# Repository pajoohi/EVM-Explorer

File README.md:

# TI EVM Explorer

A highly modular, premium-designed web application for browsing and inspecting Texas Instruments Hardware Development Kits (EVMs). 

## Features
- **Filterable/Searchable Directory**: Quickly locate evaluation modules by Processor or Board Family.
- **Detailed EVM Pages**: Dynamic specs, integrated interactive BOMs, OS downloads, and rich 3D STL visualizations.
- **Responsive & Accessible**: Native Light/Dark modes, mobile-friendly navigation, and CSS-driven component animations.

## Local Development
1. Install dependencies: `npm install`
2. Start the development server: `npm run dev`

## Deployment (GitHub Pages)
This project is configured for seamless deployment to GitHub pages using Vite and `gh-pages`.

1. Ensure the `base` property in `vite.config.js` matches your repository name (e.g., `'/EVM-Explorer/'`).
2. Run the deployment script: `npm run deploy`
   - This automatically builds the production output to the `dist/` folder and pushes it to the `gh-pages` branch.

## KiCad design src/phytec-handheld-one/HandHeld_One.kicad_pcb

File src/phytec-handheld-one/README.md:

# PHYTEC Handheld One

The **PHYTEC Handheld One** is a functional handheld gaming device developed in under six weeks as a proof-of-concept for PHYTEC's System-on-Module (SoM) design approach, and showcased at **Embedded World**. It demonstrates how pre-engineered hardware can accelerate the journey from a breadboard prototype to a custom, bootable system.

## Overview

This repository contains the design files and documentation used to build the Handheld One. The project highlights the advantages of using a SOM over a discrete chip-down design, allowing for rapid iteration and scalability.

## Key Features

* **Rapid prototyping:** Concept to custom carrier board in under six weeks.
* **Gaming-ready Linux stack:** RetroArch (GLES3) with libretro cores, Freedoom, Chocolate Doom, SuperTuxKart, and Neverball, all launched from a custom touchscreen UI.
* **Integrated peripherals:** Touchscreen, gamepad inputs (D-pad / face buttons) via the MSPM0 companion MCU.

## Hardware Architecture

The Handheld One is built around the PHYTEC SOM ecosystem. By utilizing a standardized footprint, the carrier board can accommodate different performance tiers without requiring a complete redesign.

Designed in **KiCad 9.0**, the Schematics (`.kicad_sch`) and PCB layout (`.kicad_pcb`) live in the hardware repo below.

## Software

The Handheld One runs a **Yocto** based Linux distribution (scarthgap). The `meta-handheld-one` layer pulls in the launcher, retro gaming stack, Wayland/Weston graphics, and the AM62Px 3D demo.

## Repositories

- **[`phytec-handheld-one`](https://github.com/phytec-labs/phytec-handheld-one)** — Hardware design (KiCad schematics and PCB layout)
- **[`meta-handheld-one`](https://github.com/phytec-labs/meta-handheld-one/tree/scarthgap)** — Yocto meta-layer that builds the full image (use the `manifests` branch for repo-based checkout)
- **[`phytec-handheld-launcher`](https://github.com/phytec-labs/phytec-handheld-launcher/tree/scarthgap)** — Touchscreen launcher that runs at boot and starts the gaming stack
- **[`phytec-handheld-mspm0-driver`](https://github.com/phytec-labs/phytec-handheld-mspm0-driver)** — Firmware/drivers for the MSPM0 companion MCU (flashed manually, outside Yocto)

## Getting Started

Clone whichever piece you need:

```bash
# Hardware (KiCad 9.0+)
git clone https://github.com/phytec-labs/phytec-handheld-one.git

# Yocto BSP layer (scarthgap)
git clone -b scarthgap https://github.com/phytec-labs/meta-handheld-one.git

# Launcher
git clone -b scarthgap https://github.com/phytec-labs/phytec-handheld-launcher.git

# MSPM0 firmware
git clone https://github.com/phytec-labs/phytec-handheld-mspm0-driver.git
```

For a full Yocto build, use the `manifests` branch of `meta-handheld-one` to fetch all required layers via `phyLinux init -x`.

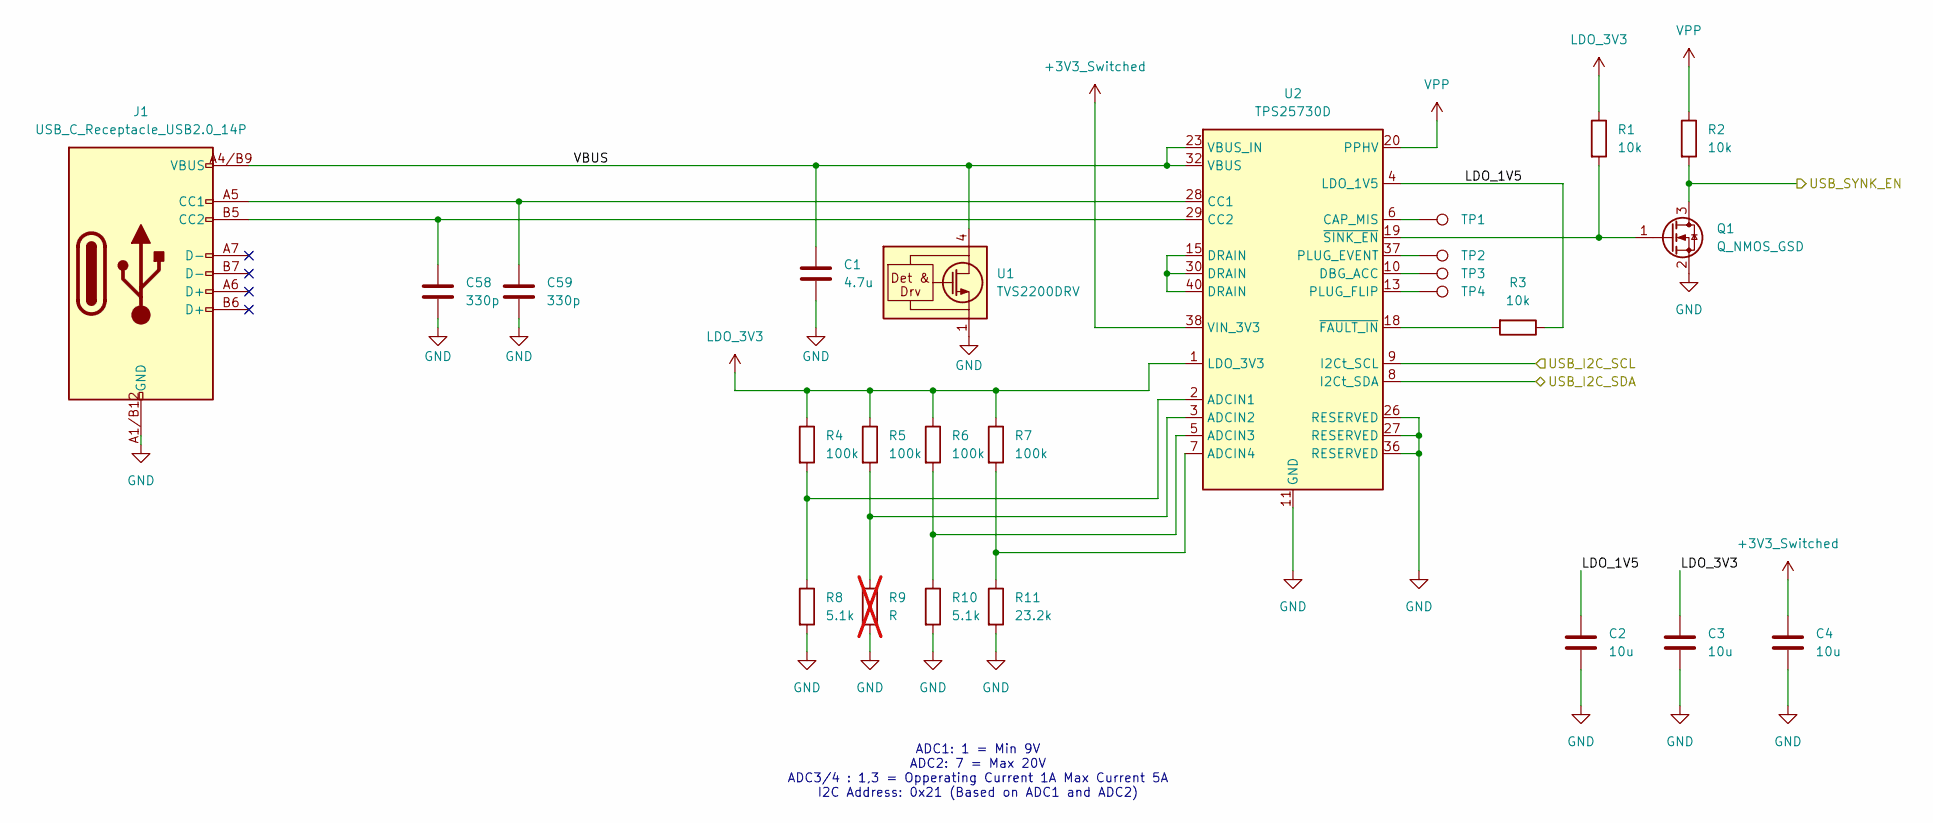
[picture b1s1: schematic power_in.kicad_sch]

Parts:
C1: 4.7u; C_0402_1005Metric_Pad0.74x0.62mm_HandSolder
C2, C3, C4: 10u; C_0402_1005Metric_Pad0.74x0.62mm_HandSolder
C58, C59: 330p; C_0402_1005Metric_Pad0.74x0.62mm_HandSolder
J1: USB_C_Receptacle_USB2.0_14P; CONN_8p94X6p5X3p16_12L_GCC
Q1: Q_NMOS_GSD; SC-59_Handsoldering
R1, R2, R3: 10k; R_0402_1005Metric_Pad0.72x0.64mm_HandSolder
R4, R5, R6, R7: 100k; R_0402_1005Metric_Pad0.72x0.64mm_HandSolder
R8, R10: 5.1k; R_0402_1005Metric_Pad0.72x0.64mm_HandSolder
R9: R; R_0402_1005Metric_Pad0.72x0.64mm_HandSolder; not fitted
R11: 23.2k; R_0402_1005Metric_Pad0.72x0.64mm_HandSolder
TP1, TP2, TP3, TP4: TestPoint; TestPoint_Pad_D1.0mm
U1: TVS2200DRV; WSON-6-1EP_2x2mm_P0.65mm_EP1x1.6mm
U2: TPS25730D; Texas_REF0038A_WQFN-38-2EP_6x4mm_P0.4

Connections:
+3V3_Switched: C4.1, U2.38 (VIN_3V3); also elsewhere on the board
/Audio/Audio_I2C_SCL: U2.9 (I2Ct_SCL); also elsewhere on the board
/Audio/Audio_I2C_SDA: U2.8 (I2Ct_SDA); also elsewhere on the board
/Power In/LDO_1V5: C2.1, R3.1, U2.4 (LDO_1V5)
/Power In/USB_SYNK_EN: Q1.3 (D), R2.2; also elsewhere on the board
/Power In/VBUS: C1.1, J1.A4/B9 (VBUS), J1.B4/A9 (VBUS), U1.4 (IN), U1.5 (IN), U1.6 (IN), U2.23 (VBUS_IN), U2.32 (VBUS)
GND: C1.2, C2.2, C3.2, C4.2, C58.2, C59.2, J1.A1/B12 (GND), J1.B1/A12 (GND), Q1.2 (S), R8.2, R9.2, R10.2, R11.2, U1.1 (GND), U1.2 (GND), U1.3 (GND), U1.7 (GND), U2.11 (GND), U2.12 (GND), U2.14 (GND), U2.16 (GND), U2.17 (GND), U2.26 (RESERVED), U2.27 (RESERVED), U2.31 (GND), U2.34 (GND), U2.36 (RESERVED), U2.39 (GND); also elsewhere on the board
LDO_3V3: C3.1, R1.1, R4.1, R5.1, R6.1, R7.1, U2.1 (LDO_3V3)
unnamed: C59.1, J1.A5 (CC1), U2.28 (CC1)
unnamed: C58.1, J1.B5 (CC2), U2.29 (CC2)
unnamed: Q1.1 (G), R1.2, U2.19 (~SINK_EN)
unnamed: R4.2, R8.1, U2.2 (ADCIN1)
unnamed: R5.2, R9.1, U2.3 (ADCIN2)
unnamed: R6.2, R10.1, U2.5 (ADCIN3)
unnamed: R7.2, R11.1, U2.7 (ADCIN4)
unnamed: TP1.1, U2.6 (CAP_MIS)
unnamed: TP3.1, U2.10 (DBG_ACC)
unnamed: U2.15 (DRAIN), U2.30 (DRAIN), U2.40 (DRAIN)
unnamed: TP2.1, U2.37 (PLUG_EVENT)
unnamed: TP4.1, U2.13 (PLUG_FLIP)
unnamed: R3.2, U2.18 (~FAULT_IN)
VPP: R2.1, U2.20 (PPHV); also elsewhere on the board

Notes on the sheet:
ADC1: 1 = Min 9V ADC2: 7 = Max 20V ADC3/4 : 1,3 = Opperating Current 1A Max Current 5A I2C Address: 0x21 (Based on ADC1 and ADC2)

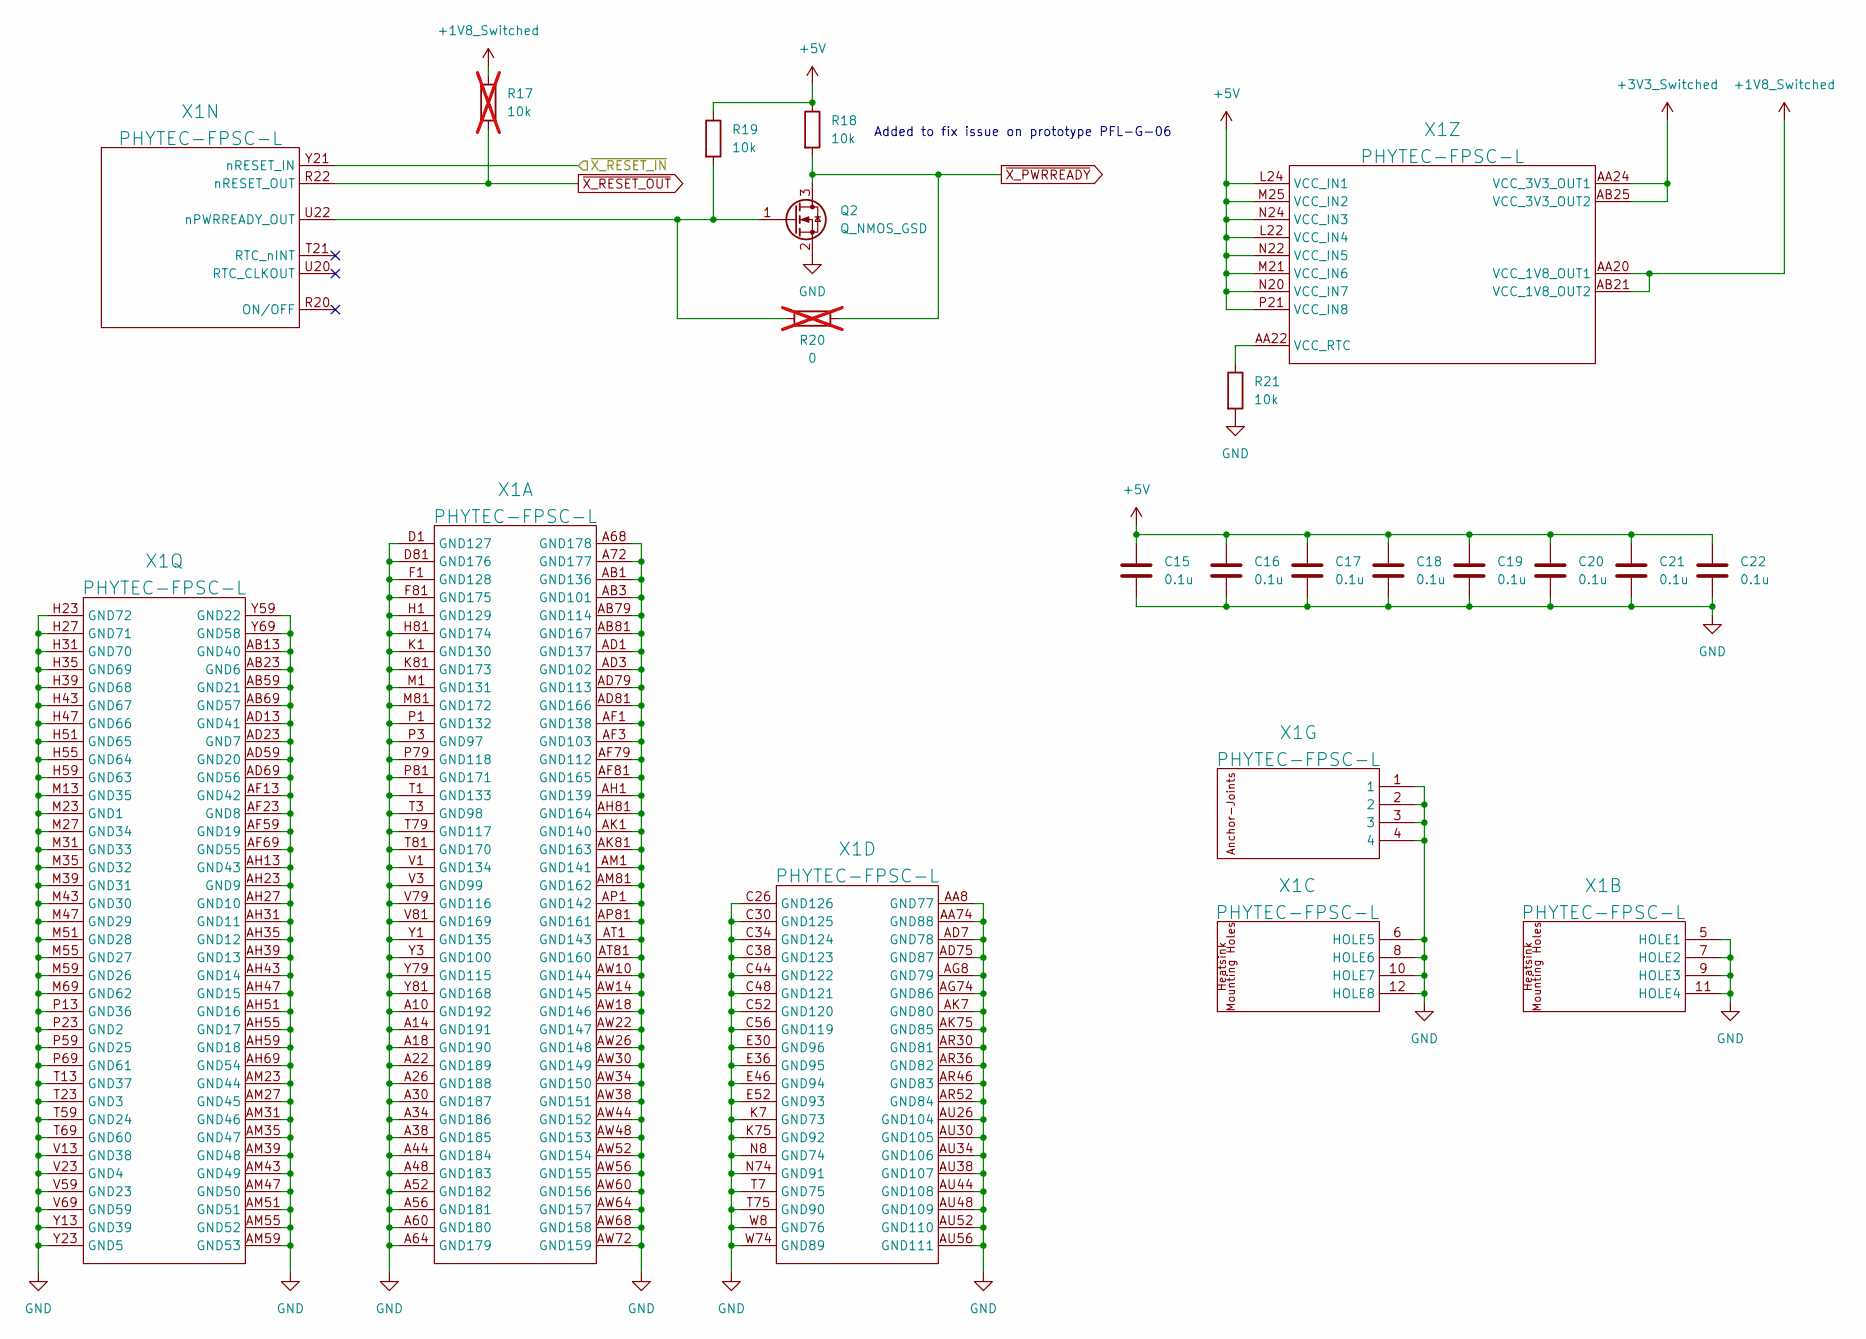
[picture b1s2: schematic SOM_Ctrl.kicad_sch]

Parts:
C15, C16, C17, C18, C19, C20, C21, C22: 0.1u; C_0402_1005Metric_Pad0.74x0.62mm_HandSolder
Q2: Q_NMOS_GSD; SC-59_Handsoldering
R17: 10k; R_0402_1005Metric_Pad0.72x0.64mm_HandSolder; not fitted
R18, R19, R21: 10k; R_0402_1005Metric_Pad0.72x0.64mm_HandSolder
R20: 0; R_0402_1005Metric_Pad0.72x0.64mm_HandSolder; not fitted
X1: PHYTEC-FPSC-L; PHYTEC-FPSC-BASIS-L-Socket

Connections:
+1V8_Switched: R17.1, X1.AA20 (VCC_1V8_OUT1), X1.AB21 (VCC_1V8_OUT2); also elsewhere on the board
+3V3_Switched: X1.AA24 (VCC_3V3_OUT1), X1.AB25 (VCC_3V3_OUT2); also elsewhere on the board
+5V: C15.1, C16.1, C17.1, C18.1, C19.1, C20.1, C21.1, C22.1, R18.1, R19.1, X1.L22 (VCC_IN4), X1.L24 (VCC_IN1), X1.M21 (VCC_IN6), X1.M25 (VCC_IN2), X1.N20 (VCC_IN7), X1.N22 (VCC_IN5), X1.N24 (VCC_IN3), X1.P21 (VCC_IN8); also elsewhere on the board
/Powre Reg/PGOOD: X1.Y21 (nRESET_IN); also elsewhere on the board
GND: C15.2, C16.2, C17.2, C18.2, C19.2, C20.2, C21.2, C22.2, Q2.2 (S), R21.2, X1.1, X1.2, X1.3, X1.4, X1.5 (HOLE1), X1.6 (HOLE5), X1.7 (HOLE2), X1.8 (HOLE6), X1.9 (HOLE3), X1.10 (HOLE7), X1.11 (HOLE4), X1.12 (HOLE8), X1.A10 (GND192), X1.A14 (GND191), X1.A18 (GND190), X1.A22 (GND189), X1.A26 (GND188), X1.A30 (GND187), X1.A34 (GND186), X1.A38 (GND185), X1.A44 (GND184), X1.A48 (GND183), X1.A52 (GND182), X1.A56 (GND181), X1.A60 (GND180), X1.A64 (GND179), X1.A68 (GND178), X1.A72 (GND177), X1.AA8 (GND77), X1.AA74 (GND88), X1.AB1 (GND136), X1.AB3 (GND101), X1.AB13 (GND40), X1.AB23 (GND6), X1.AB59 (GND21), X1.AB69 (GND57), X1.AB79 (GND114), X1.AB81 (GND167), X1.AD1 (GND137), X1.AD3 (GND102), X1.AD7 (GND78), X1.AD13 (GND41), X1.AD23 (GND7), X1.AD59 (GND20), X1.AD69 (GND56), X1.AD75 (GND87), X1.AD79 (GND113), X1.AD81 (GND166), X1.AF1 (GND138), X1.AF3 (GND103), X1.AF13 (GND42), X1.AF23 (GND8), X1.AF59 (GND19), X1.AF69 (GND55), X1.AF79 (GND112), X1.AF81 (GND165), X1.AG8 (GND79), X1.AG74 (GND86), X1.AH1 (GND139), X1.AH13 (GND43), X1.AH23 (GND9), X1.AH27 (GND10), X1.AH31 (GND11), X1.AH35 (GND12), X1.AH39 (GND13), X1.AH43 (GND14), X1.AH47 (GND15), X1.AH51 (GND16), X1.AH55 (GND17), X1.AH59 (GND18), X1.AH69 (GND54), X1.AH81 (GND164), X1.AK1 (GND140), X1.AK7 (GND80), X1.AK75 (GND85), X1.AK81 (GND163), X1.AM1 (GND141), X1.AM23 (GND44), X1.AM27 (GND45), X1.AM31 (GND46), X1.AM35 (GND47), X1.AM39 (GND48), X1.AM43 (GND49), X1.AM47 (GND50), X1.AM51 (GND51), X1.AM55 (GND52), X1.AM59 (GND53), X1.AM81 (GND162), X1.AP1 (GND142), X1.AP81 (GND161), X1.AR30 (GND81), X1.AR36 (GND82), X1.AR46 (GND83), X1.AR52 (GND84), X1.AT1 (GND143), X1.AT81 (GND160), X1.AU26 (GND104), X1.AU30 (GND105), X1.AU34 (GND106), X1.AU38 (GND107), X1.AU44 (GND108), X1.AU48 (GND109), X1.AU52 (GND110), X1.AU56 (GND111), X1.AW10 (GND144), X1.AW14 (GND145), X1.AW18 (GND146), X1.AW22 (GND147), X1.AW26 (GND148), X1.AW30 (GND149), X1.AW34 (GND150), X1.AW38 (GND151), X1.AW44 (GND152), X1.AW48 (GND153), X1.AW52 (GND154), X1.AW56 (GND155), X1.AW60 (GND156), X1.AW64 (GND157), X1.AW68 (GND158), X1.AW72 (GND159), X1.C26 (GND126), X1.C30 (GND125), X1.C34 (GND124), X1.C38 (GND123), X1.C44 (GND122), X1.C48 (GND121), X1.C52 (GND120), X1.C56 (GND119), X1.D1 (GND127), X1.D81 (GND176), X1.E30 (GND96), X1.E36 (GND95), X1.E46 (GND94), X1.E52 (GND93), X1.F1 (GND128), X1.F81 (GND175), X1.H1 (GND129), X1.H23 (GND72), X1.H27 (GND71), X1.H31 (GND70), X1.H35 (GND69), X1.H39 (GND68), X1.H43 (GND67), X1.H47 (GND66), X1.H51 (GND65), X1.H55 (GND64), X1.H59 (GND63), X1.H81 (GND174), X1.K1 (GND130), X1.K7 (GND73), X1.K75 (GND92), X1.K81 (GND173), X1.M1 (GND131), X1.M13 (GND35), X1.M23 (GND1), X1.M27 (GND34), X1.M31 (GND33), X1.M35 (GND32), X1.M39 (GND31), X1.M43 (GND30), X1.M47 (GND29), X1.M51 (GND28), X1.M55 (GND27), X1.M59 (GND26), X1.M69 (GND62), X1.M81 (GND172), X1.N8 (GND74), X1.N74 (GND91), X1.P1 (GND132), X1.P3 (GND97), X1.P13 (GND36), X1.P23 (GND2), X1.P59 (GND25), X1.P69 (GND61), X1.P79 (GND118), X1.P81 (GND171), X1.T1 (GND133), X1.T3 (GND98), X1.T7 (GND75), X1.T13 (GND37), X1.T23 (GND3), X1.T59 (GND24), X1.T69 (GND60), X1.T75 (GND90), X1.T79 (GND117), X1.T81 (GND170), X1.V1 (GND134), X1.V3 (GND99), X1.V13 (GND38), X1.V23 (GND4), X1.V59 (GND23), X1.V69 (GND59), X1.V79 (GND116), X1.V81 (GND169), X1.W8 (GND76), X1.W74 (GND89), X1.Y1 (GND135), X1.Y3 (GND100), X1.Y13 (GND39), X1.Y23 (GND5), X1.Y59 (GND22), X1.Y69 (GND58), X1.Y79 (GND115), X1.Y81 (GND168); also elsewhere on the board
unnamed: Q2.1 (G), R19.2, R20.1, X1.U22 (nPWRREADY_OUT)
unnamed: R21.1, X1.AA22 (VCC_RTC)
~X_PWRREADY: Q2.3 (D), R18.2, R20.2; also elsewhere on the board
~X_RESET_OUT: R17.2, X1.R22 (nRESET_OUT); also elsewhere on the board

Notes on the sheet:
Added to fix issue on prototype PFL-G-06

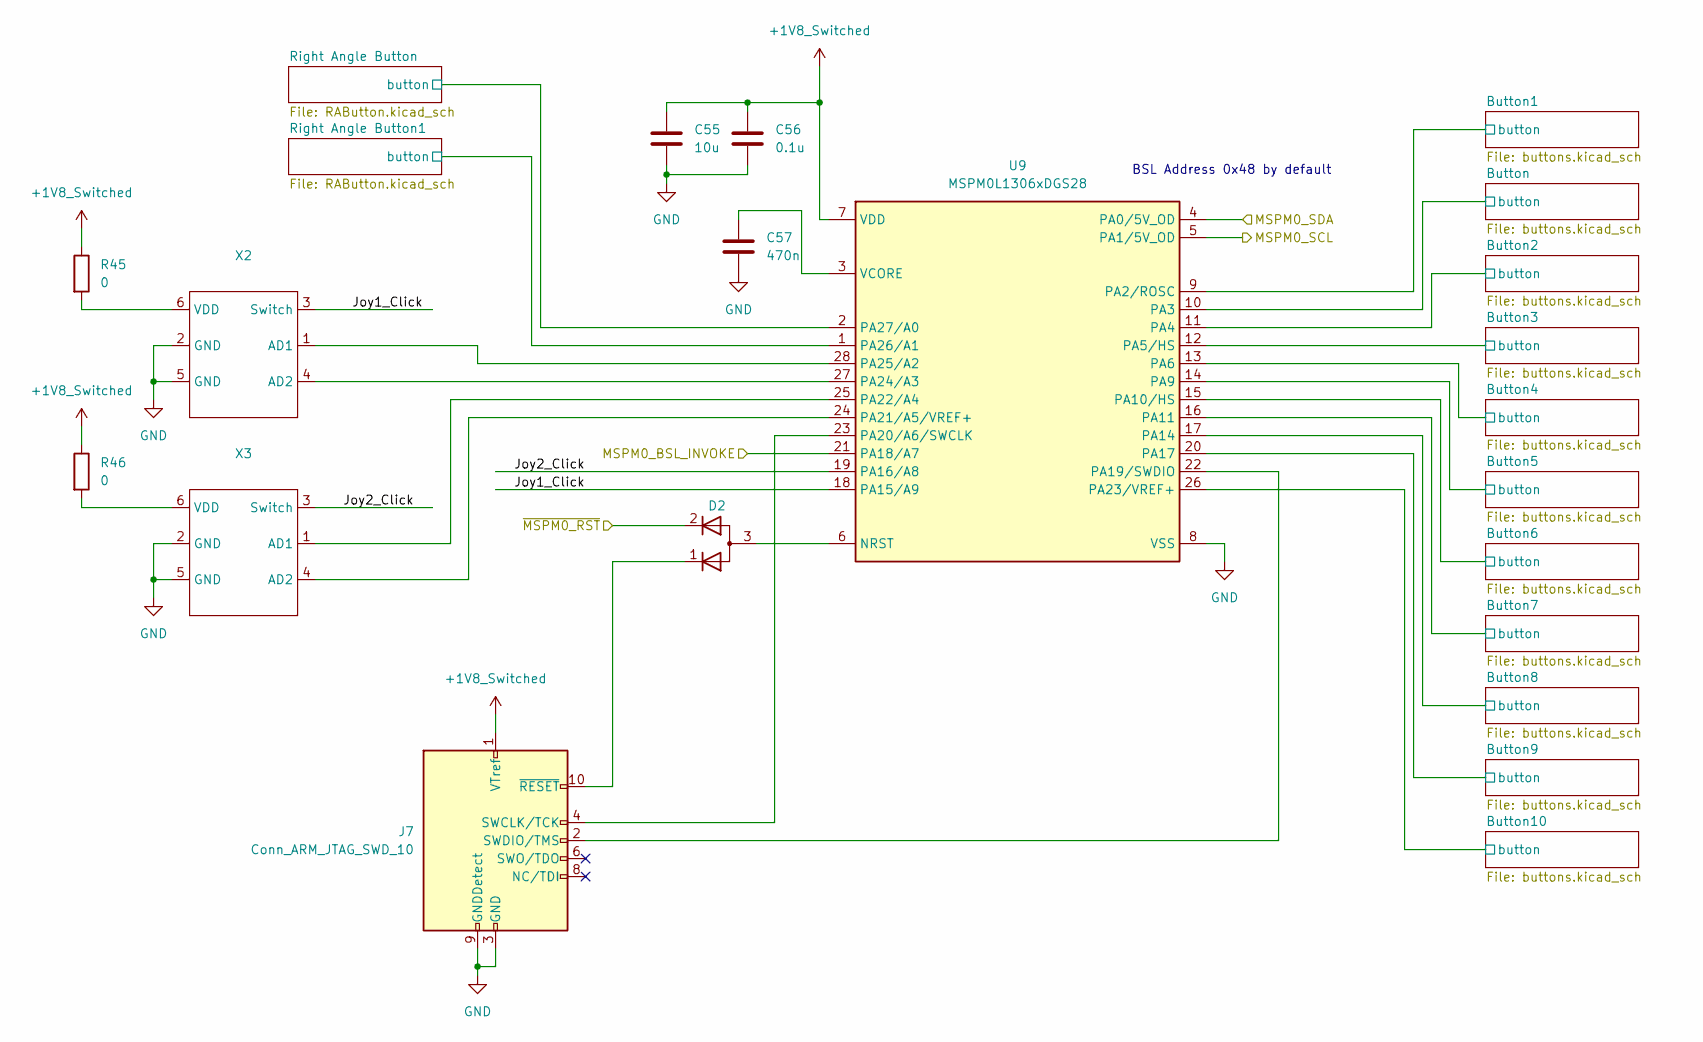
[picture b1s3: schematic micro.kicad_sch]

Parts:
C55: 10u; C_0402_1005Metric_Pad0.74x0.62mm_HandSolder
C56: 0.1u; C_0402_1005Metric_Pad0.74x0.62mm_HandSolder
C57: 470n; C_0402_1005Metric_Pad0.74x0.62mm_HandSolder
D2: D_Dual_CommonAnode_KKA_Parallel; SC-59_Handsoldering
J7: Conn_ARM_JTAG_SWD_10; PinHeader_2x05_P1.27mm_Vertical_SMD
R45, R46: 0; R_0402_1005Metric_Pad0.72x0.64mm_HandSolder
U9: MSPM0L1306xDGS28; MSPM0L130XxDGS28
X2, X3: 5628 Joystick Switches - Adafruit Industries

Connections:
+1V8_Switched: C55.1, C56.1, J7.1 (VTref), R45.1, R46.1, U9.7 (VDD); also elsewhere on the board
/IO/GPIO6: U9.21 (PA18/A7); also elsewhere on the board
/IO/GPIO7: D2.2 (K); also elsewhere on the board
/IO/I2C4_SCL: U9.5 (PA1/5V_OD); also elsewhere on the board
/IO/I2C4_SDA: U9.4 (PA0/5V_OD); also elsewhere on the board
/Micro Controller/Button1/button: U9.9 (PA2/ROSC); also elsewhere on the board
/Micro Controller/Button2/button: U9.11 (PA4); also elsewhere on the board
/Micro Controller/Button3/button: U9.12 (PA5/HS); also elsewhere on the board
/Micro Controller/Button4/button: U9.13 (PA6); also elsewhere on the board
/Micro Controller/Button5/button: U9.14 (PA9); also elsewhere on the board
/Micro Controller/Button6/button: U9.15 (PA10/HS); also elsewhere on the board
/Micro Controller/Button7/button: U9.16 (PA11); also elsewhere on the board
/Micro Controller/Button8/button: U9.17 (PA14); also elsewhere on the board
/Micro Controller/Button9/button: U9.20 (PA17); also elsewhere on the board
/Micro Controller/Button10/button: U9.26 (PA23/VREF+); also elsewhere on the board
/Micro Controller/Button/button: U9.10 (PA3); also elsewhere on the board
/Micro Controller/Joy1_Click: U9.18 (PA15/A9), X2.3 (Switch)
/Micro Controller/Joy2_Click: U9.19 (PA16/A8), X3.3 (Switch)
/Micro Controller/Right Angle Button1/button: U9.1 (PA26/A1); also elsewhere on the board
/Micro Controller/Right Angle Button/button: U9.2 (PA27/A0); also elsewhere on the board
GND: C55.2, C56.2, C57.2, J7.3 (GND), J7.5 (GND), J7.9 (GNDDetect), U9.8 (VSS), X2.2 (GND), X2.5 (GND), X3.2 (GND), X3.5 (GND); also elsewhere on the board
unnamed: D2.3 (A), U9.6 (NRST)
unnamed: J7.4 (SWCLK/TCK), U9.23 (PA20/A6/SWCLK)
unnamed: J7.2 (SWDIO/TMS), U9.22 (PA19/SWDIO)
unnamed: D2.1 (K), J7.10 (~RESET)
unnamed: U9.24 (PA21/A5/VREF+), X3.4 (AD2)
unnamed: U9.25 (PA22/A4), X3.1 (AD1)
unnamed: U9.27 (PA24/A3), X2.4 (AD2)
unnamed: U9.28 (PA25/A2), X2.1 (AD1)
unnamed: C57.1, U9.3 (VCORE)
unnamed: R45.2, X2.6 (VDD)
unnamed: R46.2, X3.6 (VDD)

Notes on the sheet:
BSL Address 0x48 by default

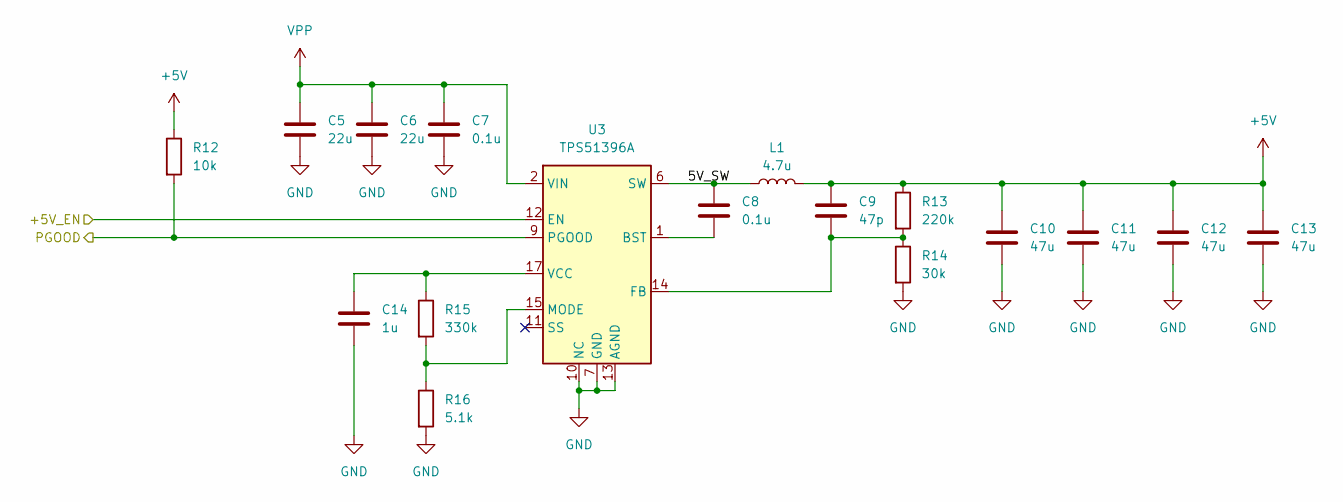
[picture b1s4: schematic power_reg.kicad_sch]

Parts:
C5, C6: 22u; C_0805_2012Metric_Pad1.18x1.45mm_HandSolder
C7, C8: 0.1u; C_0402_1005Metric_Pad0.74x0.62mm_HandSolder
C9: 47p; C_0402_1005Metric_Pad0.74x0.62mm_HandSolder
C10, C11, C12, C13: 47u; C_1206_3216Metric_Pad1.33x1.80mm_HandSolder
C14: 1u; C_0402_1005Metric_Pad0.74x0.62mm_HandSolder
L1: 4.7u; L_Coilcraft_XAL6060-XXX; MFG PN XAL6060-472MEB
R12: 10k; R_0402_1005Metric_Pad0.72x0.64mm_HandSolder
R13: 220k; R_0402_1005Metric_Pad0.72x0.64mm_HandSolder
R14: 30k; R_0402_1005Metric_Pad0.72x0.64mm_HandSolder
R15: 330k; R_0402_1005Metric_Pad0.72x0.64mm_HandSolder
R16: 5.1k; R_0402_1005Metric_Pad0.72x0.64mm_HandSolder
U3: TPS51396A; Texas_RJE0020A_VQFN-20-1EP_3x3mm_P0.45mm_EP0.675x0.76mm

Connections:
+5V: C9.1, C10.1, C11.1, C12.1, C13.1, L1.2, R12.1, R13.1; also elsewhere on the board
/Power In/USB_SYNK_EN: U3.12 (EN); also elsewhere on the board
/Powre Reg/5V_SW: C8.1, L1.1, U3.6 (SW), U3.19 (SW), U3.20 (SW)
/Powre Reg/PGOOD: R12.2, U3.9 (PGOOD); also elsewhere on the board
GND: C5.2, C6.2, C7.2, C10.2, C11.2, C12.2, C13.2, C14.2, R14.2, R16.2, U3.7 (GND), U3.8 (GND), U3.10 (NC), U3.13 (AGND), U3.16 (NC), U3.18 (GND), U3.21 (GND); also elsewhere on the board
unnamed: C8.2, U3.1 (BST)
unnamed: C9.2, R13.2, R14.1, U3.14 (FB)
unnamed: R15.2, R16.1, U3.15 (MODE)
unnamed: C14.1, R15.1, U3.17 (VCC)
VPP: C5.1, C6.1, C7.1, U3.2 (VIN), U3.3 (VIN), U3.4 (VIN), U3.5 (VIN); also elsewhere on the board

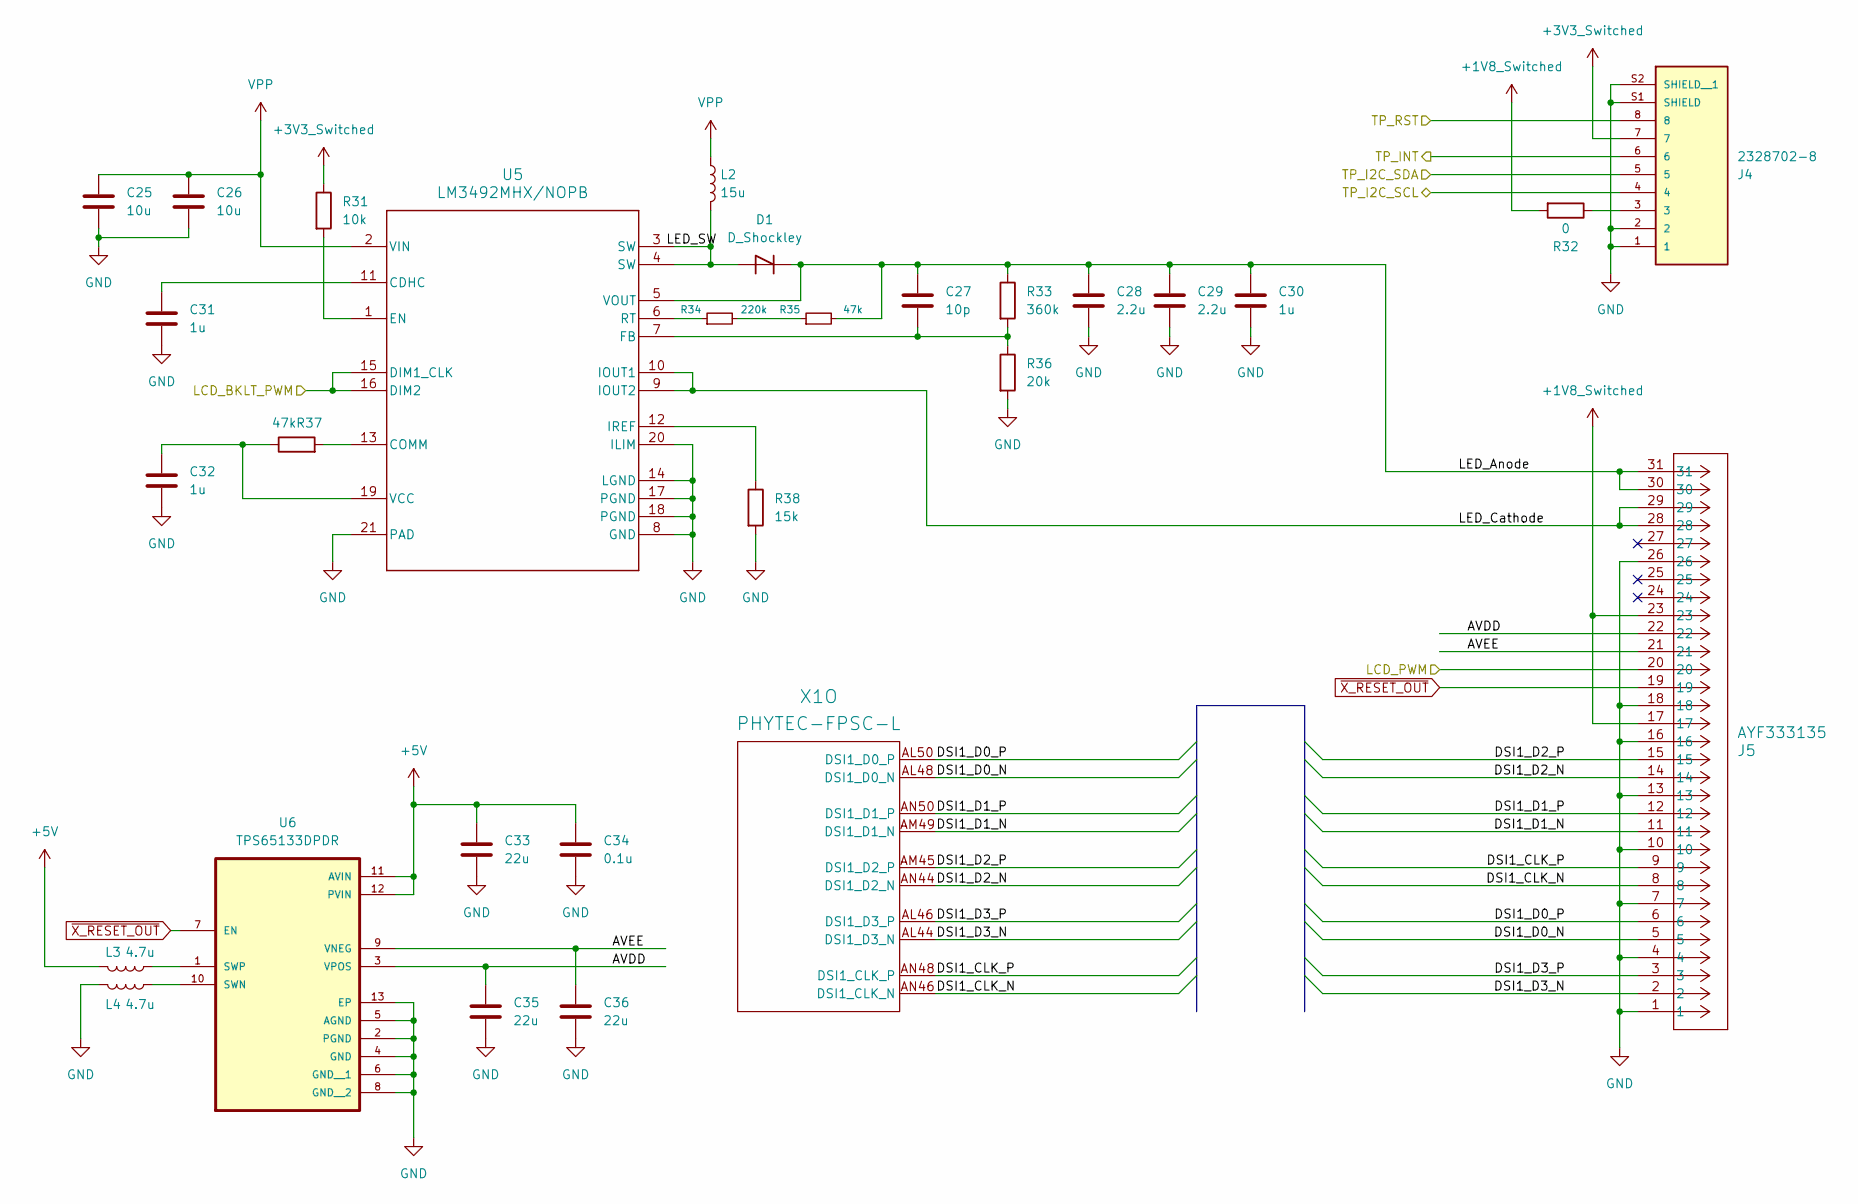
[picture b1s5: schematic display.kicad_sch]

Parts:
C25, C26: 10u; C_0402_1005Metric_Pad0.74x0.62mm_HandSolder
C27: 10p; C_0402_1005Metric_Pad0.74x0.62mm_HandSolder
C28, C29: 2.2u; C_0805_2012Metric_Pad1.18x1.45mm_HandSolder
C30: 1u; C_0805_2012Metric_Pad1.18x1.45mm_HandSolder
C31, C32: 1u; C_0402_1005Metric_Pad0.74x0.62mm_HandSolder
C33, C35, C36: 22u; C_0805_2012Metric_Pad1.18x1.45mm_HandSolder
C34: 0.1u; C_0402_1005Metric_Pad0.74x0.62mm_HandSolder
D1: D_Shockley; Vishay_SMPA
J4: 2328702-8; TE_2328702-8; PARTREV 5
J5: AYF333135; CONN_AYF333135_PAN
L2: 15u; IND_AMPLA7030Q-150MT
L3, L4: 4.7u; L_Taiyo-Yuden_NR-50xx_HandSoldering
R31: 10k; R_0402_1005Metric_Pad0.72x0.64mm_HandSolder
R32: 0; R_0402_1005Metric_Pad0.72x0.64mm_HandSolder
R33: 360k; R_0402_1005Metric_Pad0.72x0.64mm_HandSolder
R34: 220k; R_0402_1005Metric_Pad0.72x0.64mm_HandSolder
R35, R37: 47k; R_0402_1005Metric_Pad0.72x0.64mm_HandSolder
R36: 20k; R_0402_1005Metric_Pad0.72x0.64mm_HandSolder
R38: 15k; R_0402_1005Metric_Pad0.72x0.64mm_HandSolder
U5: LM3492MHX/NOPB; PWP0020A_N
U6: TPS65133DPDR; SON40P300X300X80-13N; PARTREV A
X1: PHYTEC-FPSC-L; PHYTEC-FPSC-BASIS-L-Socket

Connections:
+1V8_Switched: J5.17, J5.23, R32.2; also elsewhere on the board
+3V3_Switched: J4.7, R31.1; also elsewhere on the board
+5V: C33.1, C34.1, L3.2, U6.11 (AVIN), U6.12 (PVIN); also elsewhere on the board
/Display/AVDD: C35.1, J5.22, U6.3 (VPOS)
/Display/AVEE: C36.1, J5.21, U6.9 (VNEG)
/Display/DSI1_CLK_N: J5.8, X1.AN46 (DSI1_CLK_N)
/Display/DSI1_CLK_P: J5.9, X1.AN48 (DSI1_CLK_P)
/Display/DSI1_D0_N: J5.5, X1.AL48 (DSI1_D0_N)
/Display/DSI1_D0_P: J5.6, X1.AL50 (DSI1_D0_P)
/Display/DSI1_D1_N: J5.11, X1.AM49 (DSI1_D1_N)
/Display/DSI1_D1_P: J5.12, X1.AN50 (DSI1_D1_P)
/Display/DSI1_D2_N: J5.14, X1.AN44 (DSI1_D2_N)
/Display/DSI1_D2_P: J5.15, X1.AM45 (DSI1_D2_P)
/Display/DSI1_D3_N: J5.2, X1.AL44 (DSI1_D3_N)
/Display/DSI1_D3_P: J5.3, X1.AL46 (DSI1_D3_P)
/Display/LCD_BKLT_PWM: U5.15 (DIM1_CLK), U5.16 (DIM2); also elsewhere on the board
/Display/LCD_PWM: J5.20; also elsewhere on the board
/Display/LED_Anode: C27.1, C28.1, C29.1, C30.1, D1.1 (K), J5.30, J5.31, R33.1, R35.2, U5.5 (VOUT)
/Display/LED_Cathode: J5.28, J5.29, U5.9 (IOUT2), U5.10 (IOUT1)
/Display/TP_I2C_SCL: J4.4; also elsewhere on the board
/Display/TP_I2C_SDA: J4.5; also elsewhere on the board
/Display/TP_INT: J4.6; also elsewhere on the board
/Display/TP_RST: J4.8; also elsewhere on the board
GND: C25.2, C26.2, C28.2, C29.2, C30.2, C31.2, C32.2, C33.2, C34.2, C35.2, C36.2, J4.1, J4.2, J4.S1 (SHIELD), J4.S2 (SHIELD__1), J5.1, J5.4, J5.7, J5.10, J5.13, J5.16, J5.18, J5.26, L4.2, R36.2, R38.2, U5.8 (GND), U5.14 (LGND), U5.17 (PGND), U5.18 (PGND), U5.20 (ILIM), U5.21 (PAD), U6.2 (PGND), U6.4 (GND), U6.5 (AGND), U6.6 (GND__1), U6.8 (GND__2), U6.13 (EP); also elsewhere on the board
unnamed: D1.2 (A), L2.2, U5.3 (SW), U5.4 (SW)
unnamed: J4.3, R32.1
unnamed: R34.2, R35.1
unnamed: C31.1, U5.11 (CDHC)
unnamed: R37.2, U5.13 (COMM)
unnamed: R31.2, U5.1 (EN)
unnamed: C27.2, R33.2, R36.1, U5.7 (FB)
unnamed: R38.1, U5.12 (IREF)
unnamed: R34.1, U5.6 (RT)
unnamed: C32.1, R37.1, U5.19 (VCC)
unnamed: L4.1, U6.10 (SWN)
unnamed: L3.1, U6.1 (SWP)
VPP: C25.1, C26.1, L2.1, U5.2 (VIN); also elsewhere on the board
~X_RESET_OUT: J5.19, U6.7 (EN); also elsewhere on the board

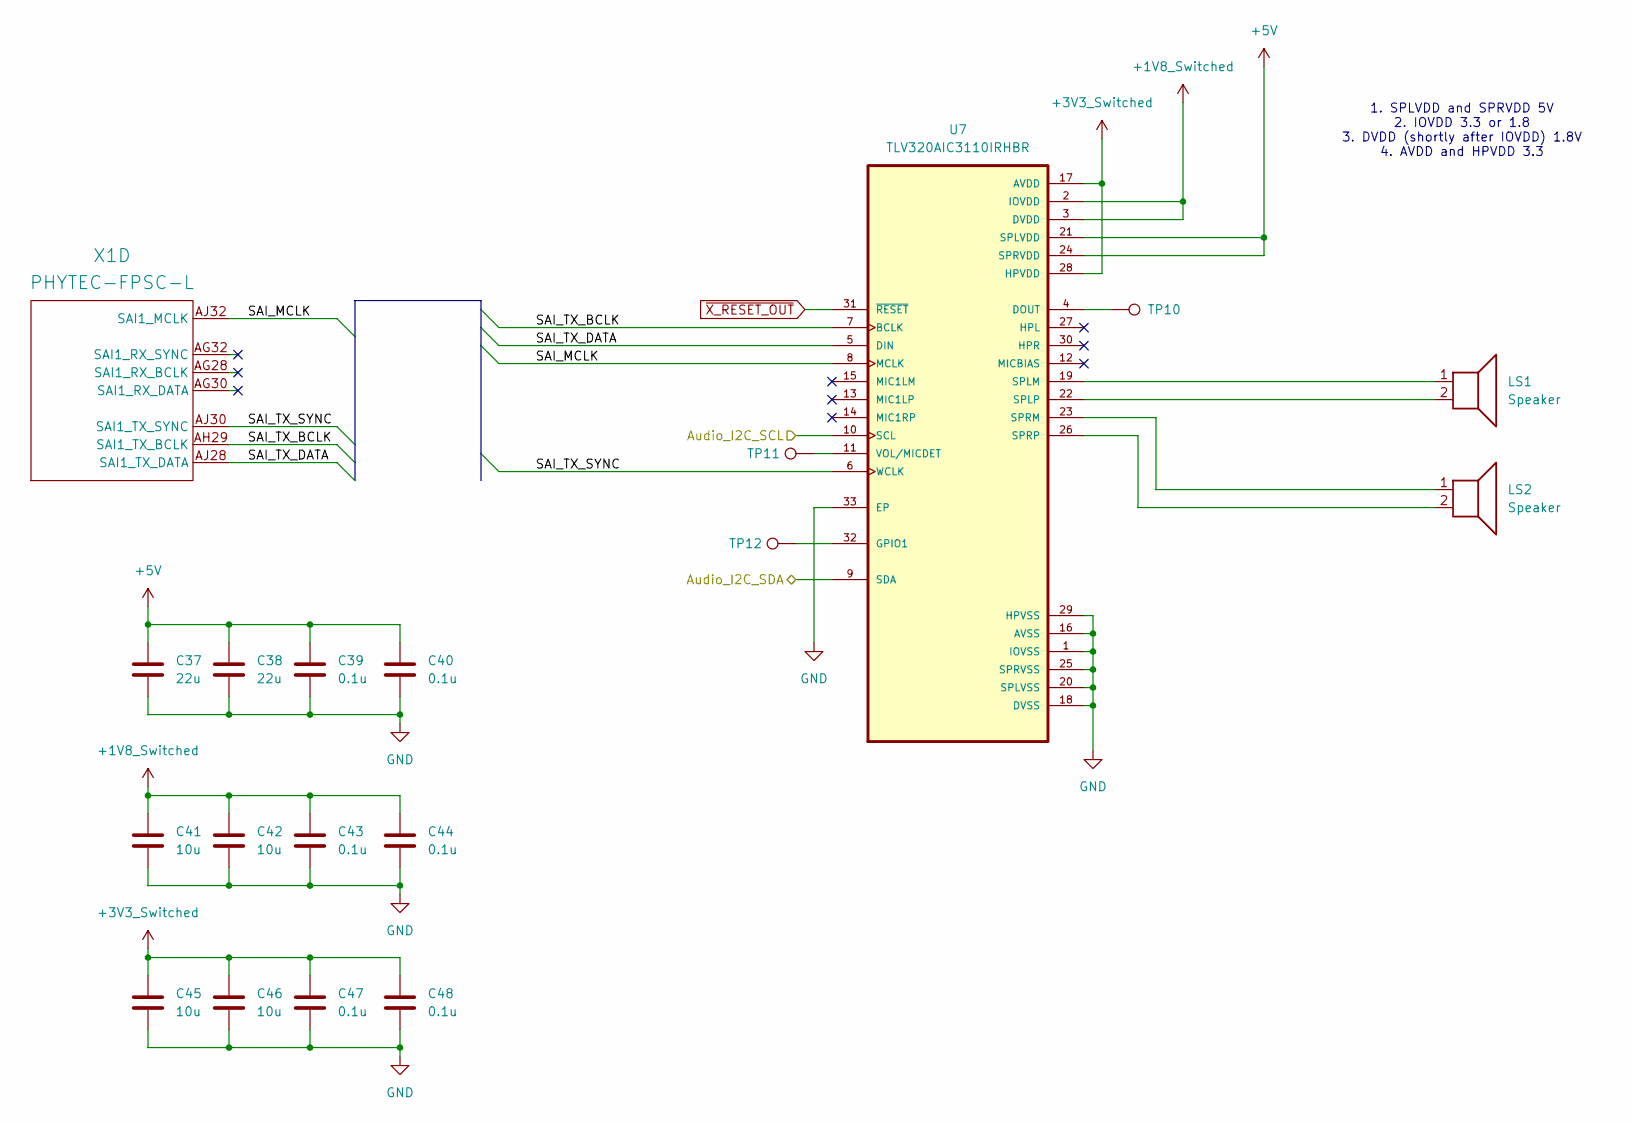
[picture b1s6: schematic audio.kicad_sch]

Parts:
C37, C38: 22u; C_0805_2012Metric_Pad1.18x1.45mm_HandSolder
C39, C40, C43, C44, C47, C48: 0.1u; C_0402_1005Metric_Pad0.74x0.62mm_HandSolder
C41, C42, C45, C46: 10u; C_0402_1005Metric_Pad0.74x0.62mm_HandSolder
LS1, LS2: Speaker; TestPoint_2Pads_Pitch2.54mm_Drill0.8mm
TP10, TP11, TP12: TestPoint; TestPoint_Pad_D1.0mm
U7: TLV320AIC3110IRHBR; IC_ADS125H01IRHBT
X1: PHYTEC-FPSC-L; PHYTEC-FPSC-BASIS-L-Socket

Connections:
+1V8_Switched: C41.1, C42.1, C43.1, C44.1, U7.2 (IOVDD), U7.3 (DVDD); also elsewhere on the board
+3V3_Switched: C45.1, C46.1, C47.1, C48.1, U7.17 (AVDD), U7.28 (HPVDD); also elsewhere on the board
+5V: C37.1, C38.1, C39.1, C40.1, U7.21 (SPLVDD), U7.24 (SPRVDD); also elsewhere on the board
/Audio/Audio_I2C_SCL: U7.10 (SCL); also elsewhere on the board
/Audio/Audio_I2C_SDA: U7.9 (SDA); also elsewhere on the board
/Audio/SAI_MCLK: U7.8 (MCLK), X1.AJ32 (SAI1_MCLK)
/Audio/SAI_TX_BCLK: U7.7 (BCLK), X1.AH29 (SAI1_TX_BCLK)
/Audio/SAI_TX_DATA: U7.5 (DIN), X1.AJ28 (SAI1_TX_DATA)
/Audio/SAI_TX_SYNC: U7.6 (WCLK), X1.AJ30 (SAI1_TX_SYNC)
GND: C37.2, C38.2, C39.2, C40.2, C41.2, C42.2, C43.2, C44.2, C45.2, C46.2, C47.2, C48.2, U7.1 (IOVSS), U7.16 (AVSS), U7.18 (DVSS), U7.20 (SPLVSS), U7.25 (SPRVSS), U7.29 (HPVSS), U7.33 (EP); also elsewhere on the board
unnamed: TP10.1, U7.4 (DOUT)
unnamed: TP12.1, U7.32 (GPIO1)
unnamed: LS1.1, U7.19 (SPLM)
unnamed: LS1.2, U7.22 (SPLP)
unnamed: LS2.1, U7.23 (SPRM)
unnamed: LS2.2, U7.26 (SPRP)
unnamed: TP11.1, U7.11 (VOL/MICDET)
~X_RESET_OUT: U7.31 (~RESET); also elsewhere on the board

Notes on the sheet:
1. SPLVDD and SPRVDD 5V 2. IOVDD 3.3 or 1.8 3. DVDD (shortly after IOVDD) 1.8V 4. AVDD and HPVDD 3.3

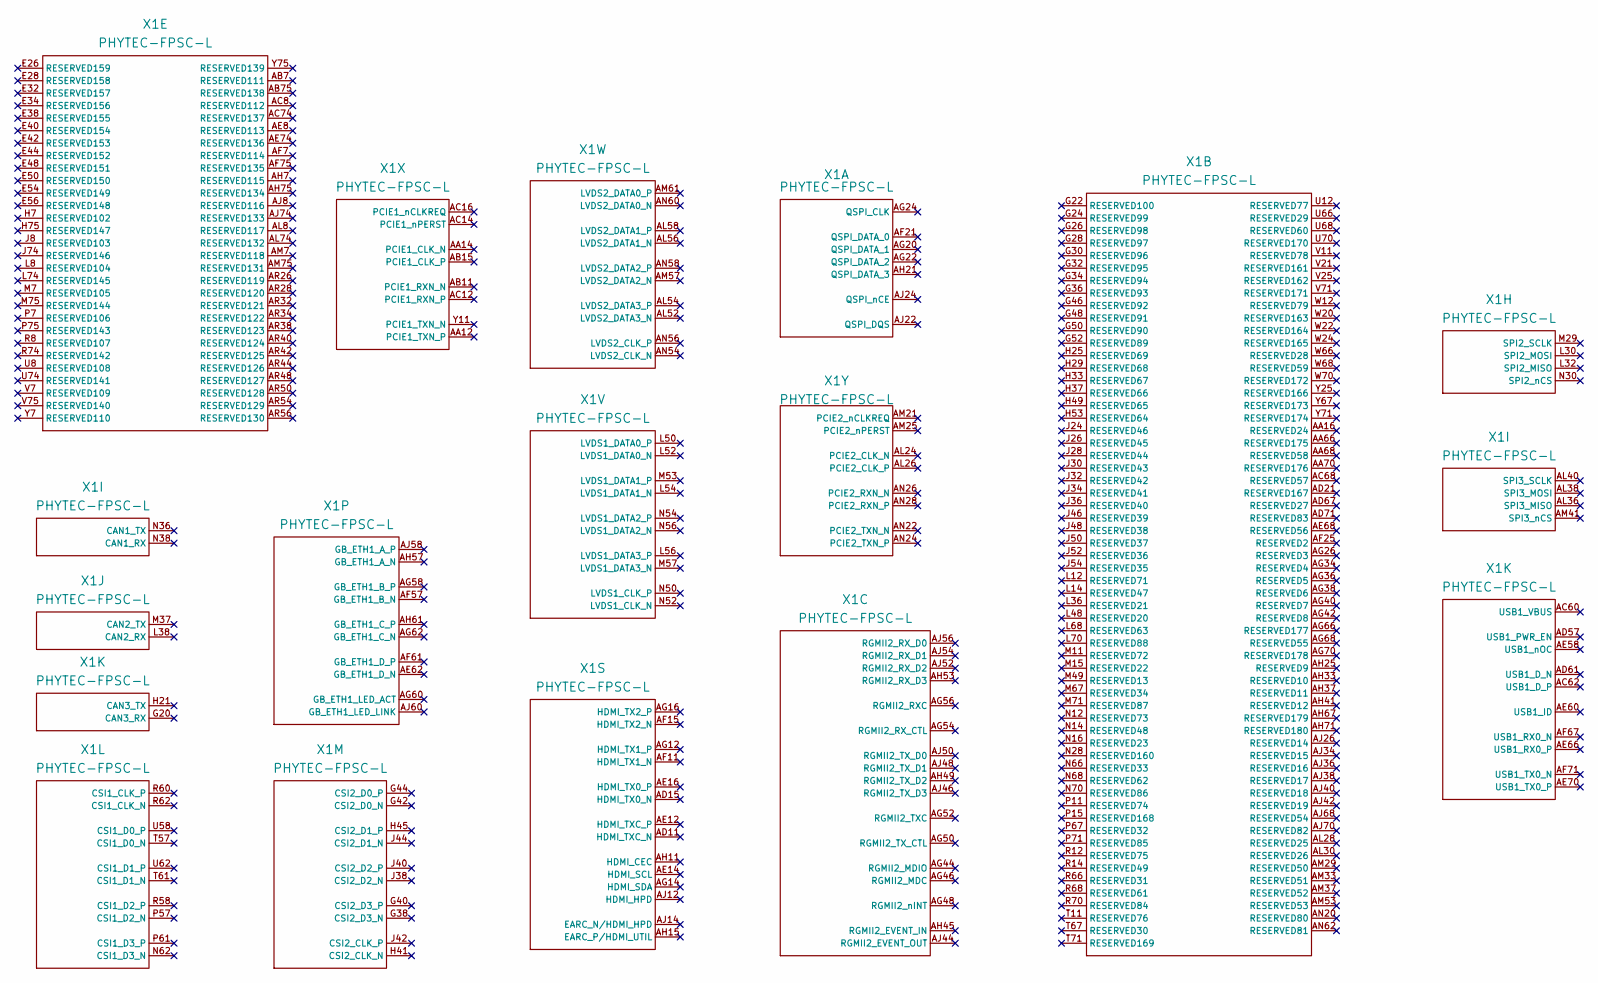
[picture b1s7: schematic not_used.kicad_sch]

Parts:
X1: PHYTEC-FPSC-L; PHYTEC-FPSC-BASIS-L-Socket
